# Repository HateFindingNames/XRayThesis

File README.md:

<!-- LTeX: language=en-EN -->

- [1. :construction: Main Document](#1-construction-main-document)
- [2. 🔩 Hardware At Hand](#2--hardware-at-hand)
  - [2.1. Source](#21-source)
    - [2.1.1. 📜 Documentation](#211--documentation)
  - [2.2. Detector](#22-detector)
    - [2.2.1. 📜 Documentation](#221--documentation)
- [3. 👀 Stuff to do](#3--stuff-to-do)
- [4. 💸 Shopping Lists](#4--shopping-lists)
  - [4.1. Hardware](#41-hardware)
  - [4.2. Fasteners](#42-fasteners)
- [5. Drafting Area](#5-drafting-area)

# 1. :construction: Main Document

Since there is no reasonable way to track updated PDFs in git I will place them on [my Onedrive :globe_with_meridians:](https://hsrheinmain-my.sharepoint.com/:b:/g/personal/lmy9f42u92_hsrheinmain_onmicrosoft_com/EdXuY1hF2GhHoTZ-xGF3LT8B4NocIp0KUSrm5S4OvCQvuw?e=4TwyDO) until it is somewhat ready to publish.

# 2. 🔩 Hardware At Hand

## 2.1. Source

**Magpro TUB00154-SA-W06:**

* XRF and X-ray imaging
* 60kV (70 keV?)
* Spot size (.25 x 1.07)mm
* Cone divergence 48°
* ~17.6e3cps @ 16.4uA (40kV)

**SA** => SPI (**S**) and Analog (**A**) control type

**W06** => Tungsten target (transmition lines provided by [NIST](https://physics.nist.gov/cgi-bin/XrayTrans/search.pl?element=W&lower=&upper=&units=eV))

Made by [Moxtek](https://moxtek.com/) and distributed (EU) by [Quantum Design](https://qd-europe.com/de/de/)

### 2.1.1. 📜 Documentation

Available documentation can be found inside this repo:

* [DATASHEET_TUB00154-SA-W06.pdf](docs/OnPaper/DATASHEET_TUB00154-SA-W06/DATASHEET_TUB00154-SA-W06.pdf)
* [MANUAL_TUB-MAN-1007.pdf](docs/OnPaper/MANUAL_TUB-MAN-1007/MANUAL_TUB-MAN-1007.pdf)
* [TUB-DATA-1013-MAGPRO.pdf](docs/Online/TUB-DATA-1013-MAGPRO.pdf)

and on my OneDrive:

* [🔒 Moxtek MagPro 70kV  XRF Source (TUB00154-XX-XXX  TUB00155-XX-XXX) Product Specification (TUB-SPEC-1033) Rev H.pdf](https://hsrheinmain-my.sharepoint.com/:b:/g/personal/lmy9f42u92_hsrheinmain_onmicrosoft_com/EV1KUsbPE4NGpiN00cES0QcBQOVuTafLMZQphgjChVBe-A?email=daniel.muenstermann%40hs-rm.de&e=YY6j7k)
* [🔒 TUB00154-XX-XXX Mechanical Drawing.pdf](https://hsrheinmain-my.sharepoint.com/:b:/g/personal/lmy9f42u92_hsrheinmain_onmicrosoft_com/Eb5gZbNKkz1OtNJbWsKaR_sB0skO_YVYC2-HvIApNUwNWA?email=daniel.muenstermann%40hs-rm.de&e=mrExvE)

## 2.2. Detector

SDD Detector made by *PN Detector*: [XRS-A (All-in-One)](https://pndetector.de/products-applications/the-xrf-spectrometer-all-in-one/)

### 2.2.1. 📜 Documentation

OneDrive:

* [🔒 User Manual - XRS-A-30-128-200-MLC+GUI 0.1.1 -3006007.pdf](https://hsrheinmain-my.sharepoint.com/:b:/g/personal/lmy9f42u92_hsrheinmain_onmicrosoft_com/EWPr4Hw9F3tDvXxqMdxp95wBGIPgKuyxWKV6rSSlt5RyFA?email=daniel.muenstermann%40hs-rm.de&e=1WMr1p)

# 3. 👀 Stuff to do

In no particular order:

* [x] Text *[Quantum Design](https://qd-europe.com/de/de/)* about
  * [x] Linux-Software available?
  
    >*"No, only Microsoft"*

    * [ ] Make custom software?
  * [x] how to switch analog <=> digital control

    >*"10-pin is programmed for either I2C, SPI or Analog at the factory.  If a customer orders with Analog, they need to run digital through the USB or send back for reprograming and testing."*

  * [x] further documentation

    >*"FYI, 12W can operate down to -5kV setting, but the spec docs currently talk to the settings for 40kV and above.  If the customer wants to operate below 40kV, the voltage is scaled linearly from 0-4.667VDC for 0 to -70kV(but will not run at all at voltages less than -4kV setting), and 0-4VDC for 0 to 1000uA current setting.  Current needs to be limited to not exceed 12W total power, so 1,000uA does not work well above 12kV setting, and they will need to reduce the emission current as they select higher kV to keep power at or below 12W.  -W06 target is really not meant to be run below 40kV, as the W coating is thick enough that it blocks a majority of the flux intensity at kV settings below 30kV.  They can run down as low as 30kV, but stability may be affected in their application below 40kV setting."*

    Additional spec sheet and drawings are made available 👌 but are classified. => Plz check [OneDrive](https://hsrheinmain-my.sharepoint.com/:f:/g/personal/lmy9f42u92_hsrheinmain_onmicrosoft_com/Eu1u_OxAc6tNtfoioA8n_JEBt5x4kzV99mTDH0zqPgQLmQ?email=daniel.muenstermann%40hs-rm.de&e=uNh9up).
  * [x] CAD files => DIY
* [ ] Enclosure options
  * [ ] [Zarges-Boxes](https://www.zarges.com/de/produkte/verpacken-transportieren/kisten)?
  * [ ] [Rüger](https://www.rueger-industriebedarf.com/) (local distributer sells them among other, cheaper brands)
  * Interior modification:
    * [ ] Interlock
    * [ ] Pb-Shielding
      * [ ] Determine necessity
      * [ ] Find distributor => pre-order
* [ ] Make CAD-Model
* [x] Detector (check [*Amptek*](https://www.amptek.com/products/x-ray-detectors/x-ray-detector-selection-guide))
  * Options:
    * ~~**Si**licon **P**ositive **I**ntrinsic **N**egative Diode (Si-PIN Diode) (Wiki: [de](https://de.wikipedia.org/wiki/Pin-Diode),[en](https://en.wikipedia.org/wiki/PIN_diode))~~
    * 👉 **S**ilicone **D**rift **D**etector (SDD) (Wiki: [de](https://de.wikipedia.org/wiki/Siliziumdriftdetektor),[en](https://en.wikipedia.org/wiki/Silicon_drift_detector))
    * ~~**Ca**dmium **Te**lluride Schottky Diode (CdTe-Schottky)~~
* [ ] X-Ray optics

# 4. 💸 Shopping Lists

## 4.1. Hardware

| **Items**                                                                                                                                                                                                                                                              |        **Moneys** | **Vendors**           |    **Ordered**     |    **Arrived**     |
| ---------------------------------------------------------------------------------------------------------------------------------------------------------------------------------------------------------------------------------------------------------------------- | ----------------: | --------------------- | :----------------: | :----------------: |
| [Ball Bearing 635-2RS](https://www.kugellager-express.de/miniatur-kugellager-635-2rs-5x19x6-mm)                                                                                                                                                                        |        10 x 0.79€ | Kugellager-Express.de | :heavy_check_mark: | :heavy_check_mark: |
| [Ball Bearing 61708](https://www.kugellager-express.de/rillenkugellager-6708-61708-2rs-40x50x6-mm)                                                                                                                                                                     |         2 x 8.20€ | Kugellager-Express.de | :heavy_check_mark: | :heavy_check_mark: |
| [PRT-01-60](https://www.igus.de/product/iglidur_PRT_01_AL_J?artnr=PRT-01-60) (Slewing Bearing)                                                                                                                                                                         |           174.78€ | Igus.de               | :heavy_check_mark: | :heavy_check_mark: |
| Drag Chain                                                                                                                                                                                                                                                             | For free :muscle: | Igus.de               | :heavy_check_mark: | :heavy_check_mark: |
| ~~[Pulley 60T](https://www.amazon.de/Saipor-Zahnriemenrad-Riemenscheibe-Synchronrad-Zahnriemenscheibe/dp/B08ZSL7BH9/ref=sr_1_2?keywords=pulley%2B60t&sr=8-2&th=1)~~ printed                                                                                            |         ~~9.79€~~ | ~~Amazon.de~~         |        :x:         |                    |
| ~~[Pulley 20T](https://www.kris3d.de/products/pulley-20t-2gt-w9-b5-black)~~                                                                                                                                                                                            |     ~~2 x 3.99€~~ | ~~kris3d.de~~         |        :x:         |                    |
| [Belt 342-2MGT3-6](https://www.keilriemenexpress.de/zahnflachriemen-zahnriemen-shop/gates-zahnriemen-powergrip-gt3/zahnflachriemen-2m-gt3/zahnflachriemen-2m-gt3-6-mm/2mgt3-342-lw-6-mm-powergripr-gt3.html) (Sample)                                                  |            12.10€ | KeilriemenExpress.de  | :heavy_check_mark: |   :heavy_check_mark:                 |
| [Belt 600-2MGT3-9](https://www.keilriemenexpress.de/zahnflachriemen-zahnriemen-shop/gates-zahnriemen-powergrip-gt3/zahnflachriemen-2m-gt3/zahnflachriemen-2m-gt3-9-mm/2mgt3-600-lw-9-mm-powergripr-gt3.html) (Detector)                                                |            16.55€ | KeilriemenExpress.de  | :heavy_check_mark: | :heavy_check_mark: |
| [Filament eSun ASA 1kg](https://www.3djake.de/esun/easa-schwarz)                                                                                                                                                                                                       |        2 x 26.99€ | 3DJake.de             | :heavy_check_mark: | :heavy_check_mark: |
| ~~[Stepper Motors](https://www.amazon.de/STEPPERONLINE-Schrittmotor-55Ncm-Meter-3D-Drucker/dp/B0B93HTR87/ref=sr_1_6?__mk_de_DE=%C3%85M%C3%85%C5%BD%C3%95%C3%91&crid=2FD8SIDGO2PCX&keywords=stepperonline&sprefix=stepperonline%2Caps%2C98&sr=8-6&th=1)~~ self supplied |    ~~2 x 10.99€~~ | ~~Amazon.de~~         |        :x:         |                    |
| ~~[PSU 5V](https://www.digikey.de/en/products/detail/mean-well-usa-inc/RS-25-5/7706180)~~                                                                                                                                                                              |        ~~14.23€~~ | ~~Digikey.de~~        | :heavy_check_mark: | :heavy_check_mark:                   |
| ~~[PSU 24V](https://www.digikey.de/en/products/detail/mean-well-usa-inc/LRS-150-24/7705015)~~                                                                                                                                                                          |        ~~26.54€~~ | ~~Digikey.de~~        | :heavy_check_mark: | :heavy_check_mark:                   |
| [Aluminum Box](https://www.aluboxen-shop.de/aluboxen-mit-deckel/alukiste-xxl-130-liter)                                                                                                                                                                                |            99.90€ | aluboxen-shop.de      | :heavy_check_mark: |   :heavy_check_mark:                 |
| [Aluminum EN AW 5083 (8x505x770)mm](https://www.gemmel-metalle.de/aluminium/platten/5083/aluminiumplatte-213.html)                                                                                                                                                     |            96.70€ | gemmel-metalle.de     | :heavy_check_mark: |  :heavy_check_mark:                  |
| [Lead Sheet (1x300x5000)mm](https://sanundo.de/sonstiges/dach-zubehoer/walzblei/56046/selbstklebendes-farbiges-walzblei-bleicolor-sk-300mm-rotbraun-aehnlich-ral-8012-meterware)                                                                                       |            112.5€ | sanundo.de            |                    |                    |
| ~~Shipping (Alu, Lead)~~                                                                                                                                                                                                                                               |        ~~99.50€~~ | gemmel-metalle.de     |                    |                    |
| [Stepper Driver](https://www.digikey.de/de/products/detail/trinamic-motion-control-gmbh/TMC2209SILENTSTEPSTICK/10232488)                                                                                                                                               |        2 x 18.22€ | digikey.de            |                    |                    |
| ~~[DAC](https://www.digikey.de/de/products/detail/microchip-technology/MCP4912-E-P/2332828)~~ Self sourced    |             ~~2.86€~~ | digikey.de            |    :heavy_check_mark:                |      :heavy_check_mark:              |
| [ADC](https://de.rs-online.com/web/p/ad-wandler/0403115?gb=s)    |        2 x 4.68€ | rs-online.com.de            |     :heavy_check_mark:               |      :heavy_check_mark:              |
| [5V Reference](https://de.rs-online.com/web/p/referenzspannungs-ics/5343065?gb=s)    |        0.83€ | rs-online.com.de            |       :heavy_check_mark:             |       :heavy_check_mark:             |
| [2.5V Reference](https://de.rs-online.com/web/p/referenzspannungs-ics/5343059?gb=s)    |        0.92€ | rs-online.com.de            |          :heavy_check_mark:          |     :heavy_check_mark:               |
| ~~**Total**~~          |   ~~**637.73€**~~ |                       |        :x:         |                    |
| **Total**              |       **718.25€** |                       |        :x:         |                    |

## 4.2. Fasteners

| **Items**                                                                                                | **Moneys** | **Vendor**        |    **Ordered**     |    **Arrived**     |
| -------------------------------------------------------------------------------------------------------- | ---------: | ----------------- | :----------------: | :----------------: |
| [M5x25 DIN912](https://www.schraubenluchs.de/100-Stueck-Zylinderschrauben-ISO-4762-DIN-912-A2-70-M-5x25) |      5.75€ | schraubenluchs.de | :heavy_check_mark: | :heavy_check_mark: |
| [M5x50 DIN912](https://www.schraubenluchs.de/100-Stueck-Zylinderschrauben-ISO-4762-DIN-912-A2-70-M-5x50) |     14.65€ | schraubenluchs.de | :heavy_check_mark: | :heavy_check_mark: |
| [M5x20 DIN912](https://www.schraubenluchs.de/100-Stueck-Zylinderschrauben-ISO-4762-DIN-912-A2-70-M-5x20) |      4.82€ | schraubenluchs.de | :heavy_check_mark: | :heavy_check_mark: |
| [M5 Hex Nut](https://www.schraubenluchs.de/200-Stueck-Sechskantmuttern-DIN-934-A2-M5)                    |      2.50€ | schraubenluchs.de | :heavy_check_mark: | :heavy_check_mark: |
| **Total**                                                                                                | **27.72€** |                   |                    |                    |

# 5. Drafting Area

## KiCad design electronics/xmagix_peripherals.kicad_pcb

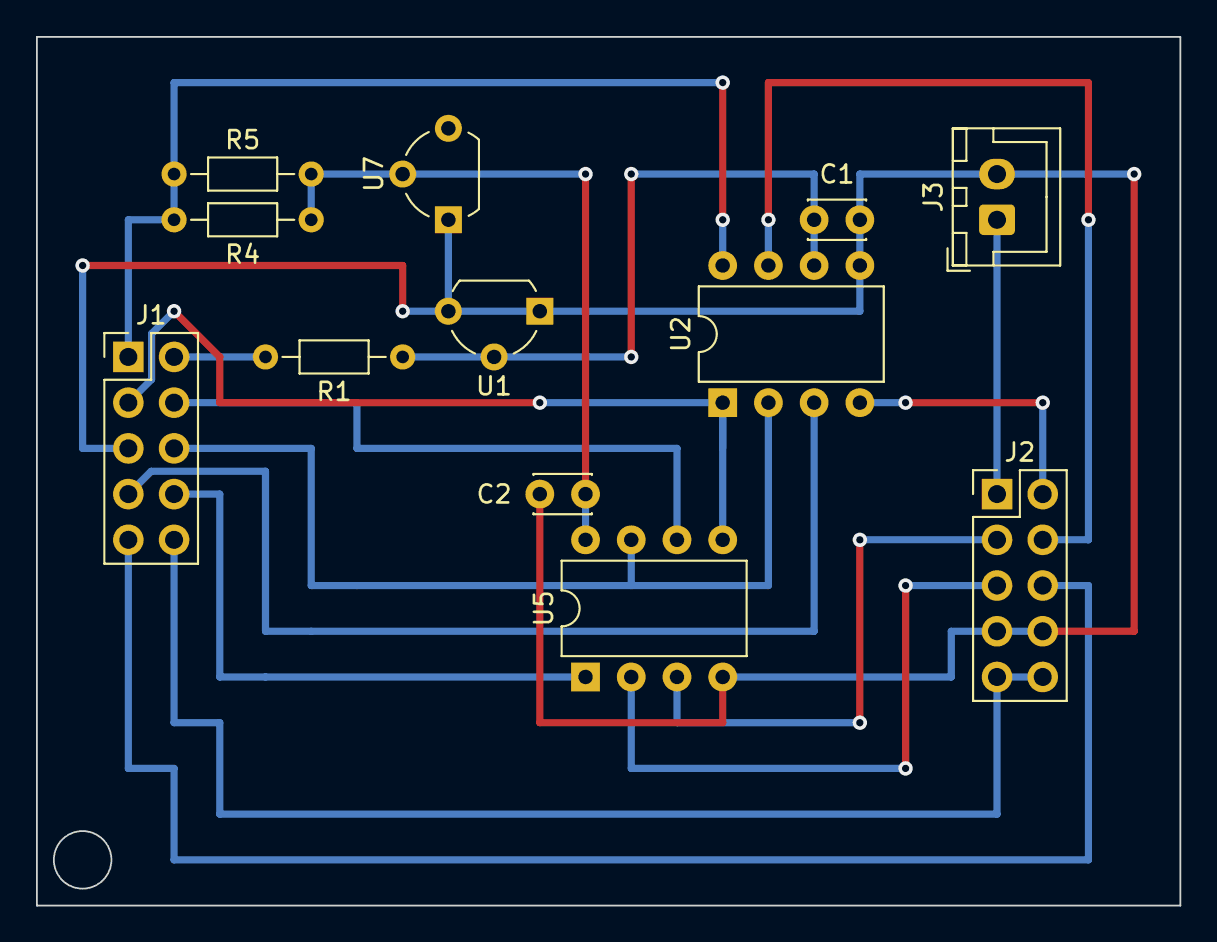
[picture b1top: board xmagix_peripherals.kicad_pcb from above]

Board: 2 copper layers, 63.5 x 48.3 mm, 12 parts (0 on the bottom side), 17 nets.

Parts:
C1, C2: 1nF; C_Disc_D3.0mm_W2.0mm_P2.54mm
J1, J2: Conn_02x05_Counter_Clockwise; PinHeader_2x05_P2.54mm_Vertical
J3: Conn_01x02; JST_XH_B2B-XH-A_1x02_P2.54mm_Vertical
R1: 470R; R_Axial_DIN0204_L3.6mm_D1.6mm_P7.62mm_Horizontal
R4, R5: 12R; R_Axial_DIN0204_L3.6mm_D1.6mm_P7.62mm_Horizontal
U1: LT1009CZ; TO-92L_Wide
U2: TLV5618A; DIP-8_W7.62mm
U5: MCP3202; DIP-8_W7.62mm
U7: LM4040LP-5; TO-92L_Wide

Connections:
+2V5A: C1.2, R1.1, U1.2 (K), U2.6 (REF)
+3.3V: J1.2, R1.2
+5V: J1.1, R4.2, R5.2, U2.8 (VDD)
+5VA: C2.1, R4.1, R5.1, U5.8 (VDD/VREF), U7.2 (K)
+24V: J2.1, J3.1
CLK: J1.6, U2.2 (SCLK), U5.7 (CLK)
Current Control: J2.4, U2.7 (OUTB)
Current Monitor: J2.3, U5.3 (CH1)
Filament Enable: J1.10, J2.9, J2.10
Filament Ready: J1.9, J2.6
GND: C1.1, C2.2, J1.5, J2.7, J2.8, J3.2, U1.1 (A), U1.3 (Adj), U2.5 (AGND), U5.4 (VSS), U7.3 (A)
HV Control: J2.2, U2.4 (OUTA)
HV Monitor: J2.5, U5.2 (CH0)
MISO: J1.4, U5.6 (DOUT)
MOSI: J1.3, U2.1 (DIN), U5.5 (DIN)
~CS0: J1.8, U5.1 (~CS/SHDN)
~CS1: J1.7, U2.3 (~CS)

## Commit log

2023-05-01 Initial
2023-05-05 Mail answers and onedrive link added.
2023-05-23 init bibliography
2023-05-25 Detector options
2023-05-25 jpg2pdf
2023-06-28 possible hyperlink fix..
2023-06-28 hyperlink fix; detector added
2023-06-29 Ruff document layout; makeindex still broken
2023-07-03 nomenclature fix; jabref config
2023-07-18 bearings..
2023-07-19 shopping list
2023-07-19 rotary stage first draft
2023-07-19 gif link fix?
2023-07-24 PRT-01-60 added; CAD updated
2023-07-24 Readability boost
2023-07-25 Shopping list updated
2023-07-27 Shopping List updates
2023-07-30 Markdown Preview GFM
2023-08-03 Table "Fasteners" added
2023-08-07 Less pricy fasteners
2023-08-11 shopping lists updated
2023-08-29 Shopping list update
2023-09-06 DAC/ADC, VRefs added
2023-09-06 Title update; Book added
2023-09-06 Schematics and Datasheets
2023-09-06 omg this setting is a blessing 🤩
2023-09-06 ADC datasheet
2023-09-13 Tube Interface Board Docs
2023-09-17 Main document, the beginning :tada:
2023-09-19 Onedrive link :globe_with_meridians: to main doc
2023-09-21 graphics and text
2023-09-22 20230922
2023-09-23 kicad custom footprints
2023-09-23 finally got part numbering right :sparkles:
2023-09-23 ger/en translation
2023-09-23 electronics; figures; tables
2023-09-23 endstops optical to tactile
2023-09-25 interface board section
2023-09-25 Top, header - re-design
2023-09-25 schematics bug fix, gitignore
2023-09-25 hardware roughly done
2023-09-25 ger/en switch removed
2023-09-25 code added, chap "software" started
2023-09-26 schematics renamed, raspi4b gpio sch added
2023-09-26 literature added/updated
2023-09-26 chap software added
2023-09-26 gitignore update
2023-09-29 electronics update/fix
2023-09-29 thetube, xmagix source
2023-09-29 klipper files moved, make config created
2023-09-29 <Tube> roughly done
2023-09-30 section kinematics
2023-09-30 title page mod
2023-09-30 software and other updates/fixes
2023-09-30 software finalized?
2023-09-30 characterization init
2023-10-02 THE declaration of independence
2023-10-02 title, quote, blank, pnumbering
2023-10-02 BOMs
2023-10-02 various smaller fixes, mods
2023-10-02 external fixes. thx suad and ben!
